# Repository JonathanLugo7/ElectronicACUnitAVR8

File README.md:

# ElectronicACUnitAVR8 Project

## Welcome

Fiat Tempra 2.0cc Electronic Air Conditioner Centralina with AVR8 MCU.  

Replacing the NEC uPD78C18 MCU with the Atmel Atmega16A AVR8 MCU.  

## Pre-requisites

* .NET Core 3.x SDK
* Angular 2.x
* Atmel Studio 7 IDE
* Microchip MPLAB X 6 IDE
* Eagle 7.5
* Arduino IDE as ISP Programmer

## Get Help

* <https://github.com/JonathanLugo7/ElectronicACUnitAVR8/tree/main/Documentation>

## Stay Informed

* [YouTube](https://www.youtube.com/channel/UC0mKs7vNITJ_Hd6y4ThR0bQ)

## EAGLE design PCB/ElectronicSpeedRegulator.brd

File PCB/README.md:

# ElectronicACUnitAVR8 - Eagle Files

Fiat Tempra 2.0cc Electronic Air Conditioner Centralina with AVR8 MCU.  

Main board, UI board and blower PWM controller eagle 7.5.x files.  

## Main board

## UI board

## Documentation is located at <https://github.com/JonathanLugo7/ElectronicACUnitAVR8/tree/main/Documentation>

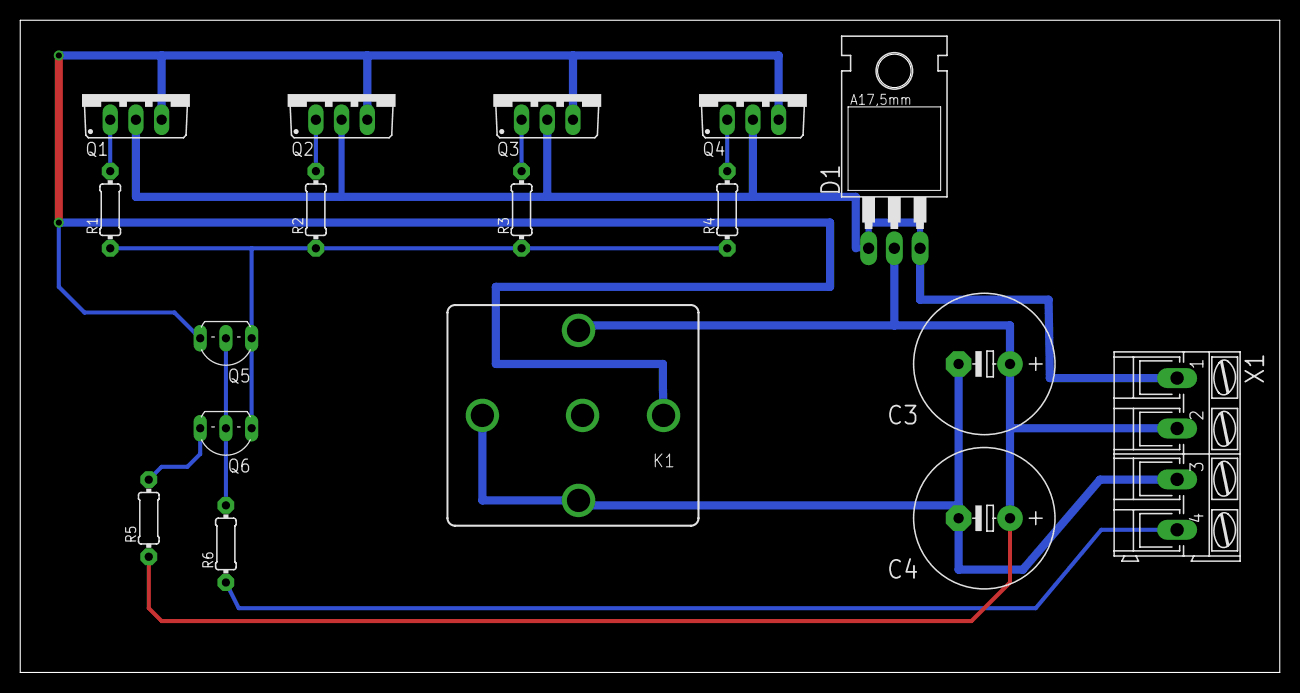
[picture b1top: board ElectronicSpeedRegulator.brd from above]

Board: 2 copper layers, 124.4 x 64.4 mm, 17 parts (0 on the bottom side), 12 nets.

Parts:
C3, C4: E5-13
D1: MUR620CT; TO220AB
K1: CB1A-P-12V; CB1
Q1, Q2, Q3, Q4: STP5NA50; TO220BV
Q5: NPN; TO92-EBC
Q6: PNP; TO92-EBC
R1, R2, R3, R4: 50; 0204/7
R5: 1.2k; 0204/7
R6: 5k; 0204/7
X1: Conn1; AK300/4

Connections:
GND: C3.-, C4.-, K1.30, K1.86, X1.3
GND_RELAY: K1.87, Q1.S, Q2.S, Q3.S, Q4.S, Q5.E
MCU_PWM_SIGNAL: R6.1, X1.4
MCU_PWM_SIGNAL_BASE: Q5.B, Q6.B, R6.2
MOSFET_DRIVER_SWITCH: Q5.C, Q6.C, R1.1, R2.1, R3.1, R4.1
MOTOR_DRIVER_V-: D1.A1, D1.A2, Q1.D, Q2.D, Q3.D, Q4.D, X1.1
unnamed: Q1.G, R1.2
unnamed: Q2.G, R2.2
unnamed: Q3.G, R3.2
unnamed: Q4.G, R4.2
S$3: Q6.E, R5.2
V+: C3.+, C4.+, D1.C, K1.85, R5.1, X1.2

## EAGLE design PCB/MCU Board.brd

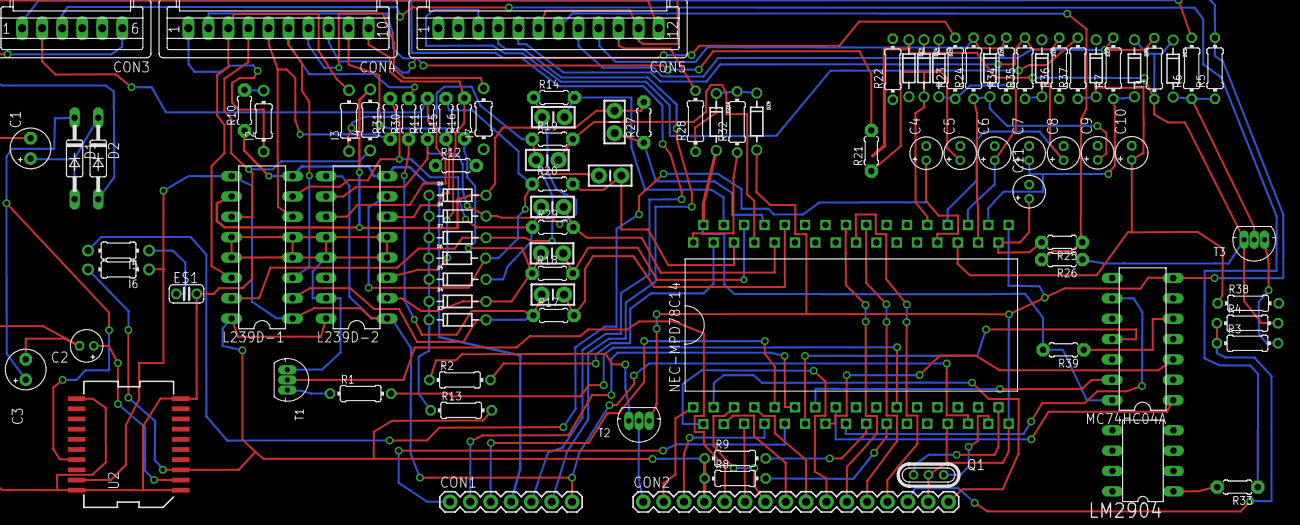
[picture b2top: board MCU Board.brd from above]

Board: 2 copper layers, 99 parts (0 on the bottom side), 91 nets.

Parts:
C1: E2,5-5
C2: 100nF; E1,8-4
C3: 47uF; E2,5-5
C4, C5, C6, C7, C8, C9, C10, C11: 2.2uF; E1,8-4
CON1: 1X07
CON2: 1X16
CON3: S06P
CON4: S10P
CON5: S12P
D1, D2: DO35-10
D3, D4, D5, D6, D7, D8, D9: DIODE-ZENER
DZ1, DZ2, DZ3, DZ4, DZ5, DZ6, DZ7, DZ8, DZ9, DZ10: DIODE-ZENER
E$1: C025-024X044
E$8, E$9, E$10, E$11, E$12, E$13, E$14: CAP-PTH-SMALL-KIT
I1: 16.5K; 0204/7
I2, I3, I4, I5, I6, I7: TFI0204
L239D-1: AirDistMotor & AirCock&BlendMotor; DIL16
L239D-2: AirIntakeMotor & ThreeLevelPressureSW; DIL16
LM2904: LM2904; DIP08
MC74HC04A: DIL14
NEC-MPD78C14: mPD78C14; P64GQ-100-36
Q1: 8MHz; UM5
R1, R2: 330; 0204/7
R3: 82K; 0204/7
R4, R38: 12K; 0204/7
R5, R6, R7, R23, R24, R28, R35: 22K; 0204/7
R8, R9: 8.2K; 0204/7
R10: 5K7; 0204/5
R11, R12, R15, R16, R30, R31: 8K2; 0204/5
R13: 180; 0204/7
R14, R17, R18, R19, R20, R21, R27, R29, R33, R39: 22K; 0204/5
R22, R32: 8K2; 0204/7
R25: 22K +/-5%; 0204/5
R26: 1500; 0204/5
R34: 3.92k; 0204/7
R36: 3.92K; 0204/7
R37: 22.1K; 0204/7
T1: LCD Vel.; SOT54
T2: LCD Temp; SOT54
T3: Bright Ctrl.; SOT54
U2: ST-L4947PD; POWERSO-20

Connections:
CON5.7[BL].PASSENGER_COMPARTMENT_TEMP_SENSOR->MPD78C14.AN0: CON5.7, R25.1, R26.2
CON5.8[B].OUTSIDE_MIRROR_TEMP_SENSOR->MPD78C14.AN1: CON5.8, I1.2, R7.2
L239D.A1<-MPD78C14.PD0: D3.P$2, E$12.1, L239D-1.2, R17.1, R30.1
L239D.A1<-MPD78C14.PD4: D4.P$2, E$11.1, L239D-2.2, R16.1, R18.1
L239D.A2<-MPD78C14.PD1: D5.P$2, E$10.1, L239D-1.7, R29.1, R31.2
L239D.A2<-MPD78C14.PD2: E$14.1, NEC-MPD78C14.P$57, R27.1
L239D.A2<-MPD78C14.PD5: D6.P$2, E$13.1, L239D-2.7, R15.2, R20.1
L239D.A3<-MPD78C14.PD2: D9.P$2, E$14.2, I4.2, L239D-1.10, R27.2
L239D.A3<-MPD78C14.PD6: D8.P$2, E$8.1, L239D-2.10, R11.1, R14.1
L239D.A4<-MPD78C14.PD3: D7.P$2, E$9.1, I3.1, L239D-1.15, R19.1
L4947_VOLTAGE_REG.DELAYCAP: C2.+, U2.2
L4947_VOLTAGE_REG.RESET(+5V): CON1.7, I6.1, L239D-1.1, L239D-1.9, L239D-2.1, L239D-2.9, NEC-MPD78C14.P$28, U2.19
L4947_VOLTAGE_REG.VIN: C3.+, D1.C, U2.17
L4947_VOLTAGE_REG.VOUT(+5V): CON2.4, I6.2, L239D-1.16, L239D-2.16, R8.1, R9.1, R13.2, U2.3
L4947_VOLTAGE_REG.VOUT->MPD78C14.STOP: DZ1.P$1, DZ2.P$1, DZ3.P$1, DZ4.P$1, DZ5.P$1, I1.1, R4.2, R26.1, T3.1
LM2904.1OUT: LM2904.1, R33.2
MPD78C14.AN0: C11.+, NEC-MPD78C14.P$34, R25.2
MPD78C14.AN1: C7.+, DZ2.P$2, NEC-MPD78C14.P$35, R7.1
MPD78C14.AN2: C9.+, DZ6.P$2, NEC-MPD78C14.P$36, R24.1
MPD78C14.AN3: C6.+, DZ5.P$2, NEC-MPD78C14.P$37, R23.1
MPD78C14.AN4: C10.+, DZ7.P$2, NEC-MPD78C14.P$38, R37.1, R38.1
MPD78C14.AN5: C8.+, DZ8.P$2, NEC-MPD78C14.P$39, R35.1
MPD78C14.AN6: C4.+, I5.2, NEC-MPD78C14.P$40
MPD78C14.AN7: C5.+, DZ4.P$2, NEC-MPD78C14.P$41, R21.1
MPD78C14.PB3->MC74HC04A.A5: MC74HC04A.11, NEC-MPD78C14.P$12
MPD78C14.PB4->MC74HC04A.A6: MC74HC04A.13, NEC-MPD78C14.P$13
MPD78C14.PB5->MC74HC04A.A2: MC74HC04A.3, NEC-MPD78C14.P$14
MPD78C14.PB6->MC74HC04A.A1: MC74HC04A.1, NEC-MPD78C14.P$15
MPD78C14.PB7->MC74HC04A.A4: MC74HC04A.9, NEC-MPD78C14.P$16
MPD78C14.PC4->NPN_LCD_SPEED_BULB.BASE: NEC-MPD78C14.P$21, R1.2
MPD78C14.PD0->L239D.A1: E$12.2, NEC-MPD78C14.P$55, R17.2
MPD78C14.PD1->L239D.A2: E$10.2, NEC-MPD78C14.P$56, R29.2
MPD78C14.PD3->L239D.A4: E$9.2, NEC-MPD78C14.P$58, R19.2
MPD78C14.PD4->L239D.A1: E$11.2, NEC-MPD78C14.P$59, R18.2
MPD78C14.PD5->L239D.A2: E$13.2, NEC-MPD78C14.P$60, R20.2
MPD78C14.PD6->L239D.A3: E$8.2, NEC-MPD78C14.P$61, R14.2
MPD78C14.PD7->NPN_LCD_TEMP_BULB.BASE: NEC-MPD78C14.P$62, R2.2
MPD78C14.VDD(+5V)->MC74HC04A.A3: MC74HC04A.5, R39.1
MPD78C14.VDD(+5V)<-RADIO(+12V): NEC-MPD78C14.P$64, R32.1
MPD78C14.X1: NEC-MPD78C14.P$30, Q1.3
MPD78C14.X2: NEC-MPD78C14.P$31, Q1.1
NPN_BRIGHT_CTL.COLLECTOR(LUZ_PPL_V+): R3.2, T3.3
NPN_LCD_SPEED_BULB.BASE: R1.1, T1.1
NPN_LCD_TEMP_BULB.BASE: R2.1, T2.1
PC1/RXD: NEC-MPD78C14.P$18, R9.2
PC3/INT2: NEC-MPD78C14.P$20, R8.2
RADIO(+12V)->MPD78C14.VDD(+5V): DZ9.P$1, DZ10.P$1, R28.1, R32.2
RADIO(+12V)->MPD78C14.VDD(+5V)->MPD78C14.STOP: DZ10.P$2, MC74HC04A.14, NEC-MPD78C14.P$63, R39.2
S$4: DZ1.P$2, R5.1, R6.1, T3.2
S$7: C1.+, D1.A, D2.C
S$8: E$1.1, I5.1
S$10: D3.P$1, D4.P$1, D5.P$1, D6.P$1, D7.P$1, D8.P$1, D9.P$1, R13.1
S$28: I2.2, R10.2
[CON1.1]=MPD78C14.PB1->PCF2112_LCD_DRIVER.CLOCK_BUSTER: CON1.1, NEC-MPD78C14.P$10
[CON1.2]=MPD78C14.PB2->PCF2112_LCD_DRIVER.DATA: CON1.2, NEC-MPD78C14.P$11
[CON1.3]=MPD78C14.PB0->PCF2112_LCD_DRIVER.DATA_ENABLE: CON1.3, NEC-MPD78C14.P$9
[CON1.4][4.1]LCD_BULB_+12V-L293D_HBRIDGE_DRIVER.VCC2: CON1.4, L239D-1.8, L239D-2.8, R10.1
[CON1.6][CON5.4]=LUZ_PRINCIPAL_GND: CON1.6, CON5.4
[CON2.1]=NPN_LCD_TEMP_BULB.COLLECTOR->GND: CON2.1, T2.2
[CON2.2]=MPD78C14.PA0->KEYPAD.ROW0: CON2.2, NEC-MPD78C14.P$1
[CON2.3]=MPD78C14.PA7->KEYPAD.COL3: CON2.3, NEC-MPD78C14.P$8
[CON2.5]=NPN_LCD_SPEED_BULB.COLLECTOR->GND: CON2.5, T1.2
[CON2.6]=MPD78C14.PA5->KEYPAD.COL1: CON2.6, NEC-MPD78C14.P$6
[CON2.7]=MPD78C14.PA4->KEYPAD.COL0: CON2.7, NEC-MPD78C14.P$5
[CON2.8]=MPD78C14.PA3->KEYPAD.ROW3: CON2.8, NEC-MPD78C14.P$4
[CON2.9]=MPD78C14.PA6->KEYPAD.COL2: CON2.9, NEC-MPD78C14.P$7
[CON2.10]=MPD78C14.PA1->KEYPAD.ROW1: CON2.10, NEC-MPD78C14.P$2
[CON2.10]=MPD78C14.PF2->MM5481_LED_DRIVER.DATA_ENABLED: CON2.11, NEC-MPD78C14.P$49
[CON2.10][CON3.1]=NPN_BRIGHT_CTL.COLLECTOR->MM5481M_LED_DRIVER.BRIGHT_CONTROL(L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: CON2.14, R3.1, R4.1
[CON2.12]=MPD78C14.PF0->MM5481_LED_DRIVER.DATA: CON2.12, NEC-MPD78C14.P$47
[CON2.13]=MPD78C14.PF1->MM5481_LED_DRIVER.CLOCK_IN: CON2.13, NEC-MPD78C14.P$48
[CON2.16]=MPD78C14.PA2->KEYPAD.ROW2: CON2.16, NEC-MPD78C14.P$3
[CON3.1]->[CON1.5]=LUZ_PRINCIPAL_+12V: CON1.5, CON3.1, R6.2
[CON3.2]=L239D.3Y->THREE_LVL_PRESSURE_SW: CON3.2, L239D-2.11, R11.2
[CON3.3]=ELECTRONIC_SPEED_REG<-LM2904.1OUT: CON3.3, R33.1
[CON4.1]=LUZ_LCD_+12V: CON4.1, I2.1
[CON4.2]=COCK_BLEND_MOTOR_POT->MPD78C14.AN7: CON4.2, R21.2
[CON4.3]=L239D.4Y->AIR_COCK_BLEND_MOTOR_NEG-: CON4.3, I3.2, L239D-1.14
[CON4.4]=L239D.3Y->AIR_COCK_BLEND_MOTOR_POS+: CON4.4, I4.1, L239D-1.11
[CON4.5]=L239D.2Y->AIR_DISTR_MOTOR_NEG-: CON4.5, L239D-1.6, R31.1
[CON4.6]=L239D.1Y->AIR_DISTR_MOTOR_POS+: CON4.6, L239D-1.3, R30.2
[CON4.7]=AIR_COCK_BLEND_MOTOR-AIR_DIST_MOTOR-POT(+5V): CON4.7, I7.2
[CON4.8]=AIR_DISTR_MOTOR_POT->MPD78C14.AN3: CON4.8, R23.2
[CON4.9]=L239D.2Y->AIR_INTAKE_MOTOR_POS+: CON4.9, L239D-2.6, R15.1
[CON4.10]=L239D.1Y->AIR_INTAKE_MOTOR_NEG-: CON4.10, L239D-2.3, R16.2
[CON5.3]=ELECTR_SPEED_REG_NTC->MPD78C14.AN4: CON5.3, R37.2
[CON5.5]=->TOP_BLENDED_AIR_TEMP_SENSOR->MPD78C14.AN5: CON5.5, R35.2, R36.2
[CON5.6]=COMMON_GND: C1.-, C2.-, C3.-, CON2.15, CON3.6, CON5.6, CON5.11, DZ9.P$2, E$1.2, L239D-1.4, L239D-1.5, L239D-1.12, L239D-1.13, L239D-2.4, L239D-2.5, L239D-2.12, L239D-2.13, L239D-2.15, MC74HC04A.7, NEC-MPD78C14.P$26, NEC-MPD78C14.P$32, NEC-MPD78C14.P$33, Q1.2, R5.2, T1.3, T2.3, U2.1, U2.10, U2.11, U2.20
[CON5.9]=->BOTTOM_BLENDED_AIR_TEMP_SENSOR->MPD78C14.AN2: CON5.9, R24.2, R34.2
[CON5.10]=RADIO(+12V)->MPD78C14.VDD(+5V): CON5.10, R28.2
[CON5.12]=POWER_SUPPLIE(12V+): CON5.12, D2.A

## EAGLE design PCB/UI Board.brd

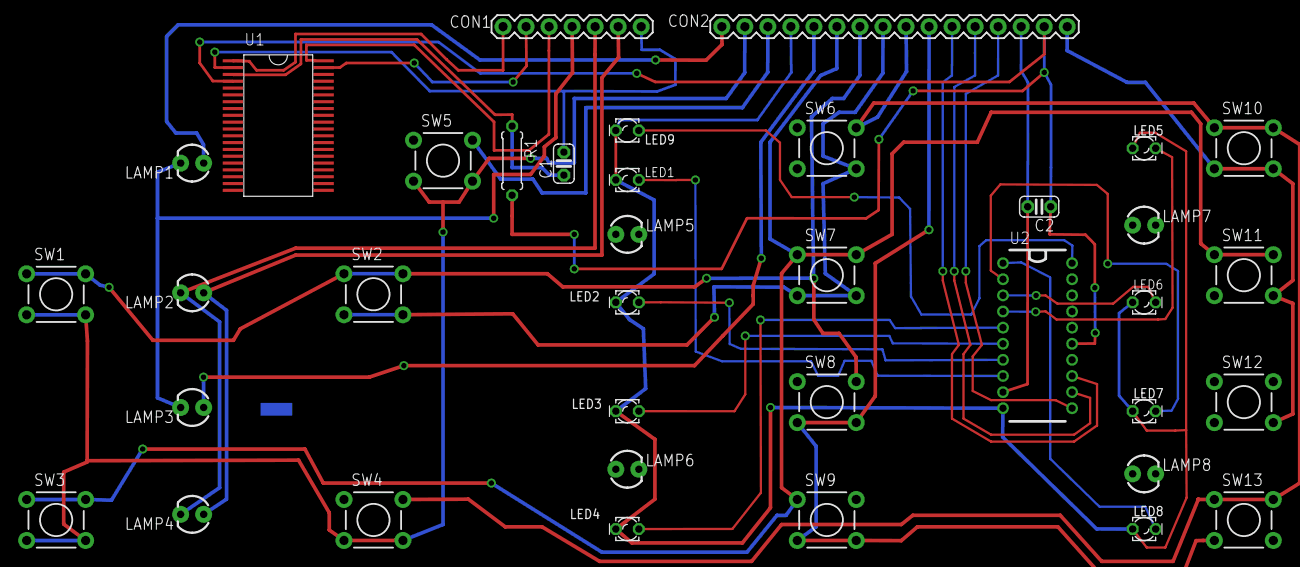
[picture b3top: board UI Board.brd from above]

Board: 2 copper layers, 37 parts (0 on the bottom side), 33 nets.

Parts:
C1, C2: 1.5nF; C025-024X044
CON1: 1X07
CON2: 1X16
LAMP1: LCD Temp; LED3MM
LAMP2, LAMP4, LAMP5, LAMP6, LAMP7, LAMP8: LIGHT; LED3MM
LAMP3: LCD SPEED; LED3MM
LED1: Auto; LED_LD260
LED2: Econ; LD260
LED3: On / Off; LD260
LED4: Off; LD260
LED5: Windsh; LD260
LED6: Front; LED_LD260
LED7: Front/Feet; LD260
LED8: Feet; LD260
LED9: On; LD260
R1: 1M; 0207/7
SW1: < Temp; TACTILE-PTH
SW2: Temp >; TACTILE-PTH
SW3: < SPEED; TACTILE-PTH
SW4: SPEED >; TACTILE-PTH
SW5: Ext.; TACTILE-PTH
SW6: Auto; TACTILE-PTH
SW7: Eco; TACTILE-PTH
SW8: Rec; TACTILE-PTH
SW9: On/Off; TACTILE-PTH
SW10: WindSh.; TACTILE-PTH
SW11: Front; TACTILE-PTH
SW12: Front+Feet; TACTILE-PTH
SW13: Feet; TACTILE-PTH
U1: PCF2112CT; SOT158-1
U2: MM5481N; PRDP0020BA-A

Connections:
CON3.1(GN)-(LUZ_PPL_V+): CON1.5, LAMP2.K, LAMP4.K
CON3.1(GN)-T3.COLLECTOR-MM5481.BRIGHT_CONTROL(LUZ_PPL_V+): C2.2, CON2.14, U2.9
CON5.4(MN)-LUZ_PPL_V-: CON1.6, LAMP2.A, LAMP4.A
CON5.11(NZ)-L4947PD(U2).GND: C2.1, CON2.15, R1.2, U1.P4, U2.15
L4947PD(U2).VOUT(+5V): CON2.4, LED1.K, LED2.K, LED3.K, LED4.K, LED5.A, LED6.A, LED7.A, LED8.A, LED9.K, U2.10
LUZ_LCD_V+: CON1.4, LAMP1.K, LAMP3.K
MM5481.LED1: LED1.A, U2.8
MM5481.LED2: LED2.A, U2.7
MM5481.LED3: LED3.A, U2.6
MM5481.LED4: LED4.A, U2.5
MM5481.LED5: LED5.K, U2.4
MM5481.LED6: LED6.K, U2.3
MM5481.LED7: LED7.K, U2.2
MM5481.LED8: LED8.K, U2.1
MM5481.LED9: LED9.A, U2.20
PA0-SW1: CON2.2, SW1.3, SW1.4, SW3.3, SW3.4, SW4.3, SW4.4, SW5.3, SW5.4
PA1-SW7: CON2.10, SW8.3, SW8.4, SW9.3, SW9.4, SW13.3
PA2-SW8: CON2.16, SW10.3, SW10.4, SW11.4, SW12.4
PA3-SW5: CON2.8, SW2.3, SW2.4, SW6.4, SW7.3, SW7.4
PA4-SW4: CON2.7, SW1.1, SW1.2, SW2.1, SW2.2, SW8.2
PA5-SW3: CON2.6, SW3.1, SW3.2, SW7.1, SW7.2, SW9.1, SW11.1, SW11.2
PA6-SW6: CON2.9, SW4.2, SW6.2, SW10.1, SW10.2, SW13.1, SW13.2
PA7-SW2: CON2.3, SW5.2
PB0-PCF2112.DATA_ENABLE: CON1.3, U1.P40
PB1-PCF2112.CLOCK_BUSTER: CON1.1, U1.P1
PB2-PCF2112.DATA: CON1.2, U1.P39
PCF2112.VDD: C1.2, CON1.7, U1.P2
PF0-MM5481.DATA: CON2.12, U2.12
PF1-MM5481.CLOCK_IN: CON2.13, U2.11
PF2-MM5481.DATA_ENABLED: CON2.11, U2.13
S$36: C1.1, R1.1, U1.P3
T1.COLLECTOR(LUZ_LCD_VELOCIDAD_V-): CON2.5, LAMP3.A
T2.COLLECTOR(LUZ_LCD_TEMPERATURA_V-): CON2.1, LAMP1.A

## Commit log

2023-08-22 jlugo: 2023-ago-21. Fiat Tempra AC Centralina with Atmel ATMega324PA (AVR8)
2023-08-22 jlugo: 2023-ago-22. Fiat Tempra AC Centralina with Atmel ATMega324PA (AVR8), minor fixes

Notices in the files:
parts and their libraries:
SparkFun-Connectors: Licensing: Creative Commons ShareAlike 4.0 International - https://creativecommons.org/licenses/by-sa/4.0
NXP_60_26022015: This library may be distributed and adapted freely for any purpose, as long as NXP is credited and any new creation is licensed under the same terms.
